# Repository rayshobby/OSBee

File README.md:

OpenSprinkler Bee (OSBee)
=========================

OpenSprinkler Bee (OSBee) is an open-source, Arduino-based sprinkler timer for battery-operated, latching solenoid valves. It's a great gadget for garden and lawn watering, plant and flower irrigation, and other watering applications. We provide two versions: 

- OSBee Shield: an Arduino shield with 4 independent zones
- OSBee: a standalone sprinkler timer with 4 independent zones and a 2.4GHz transceiver, powered by two AA batteries.

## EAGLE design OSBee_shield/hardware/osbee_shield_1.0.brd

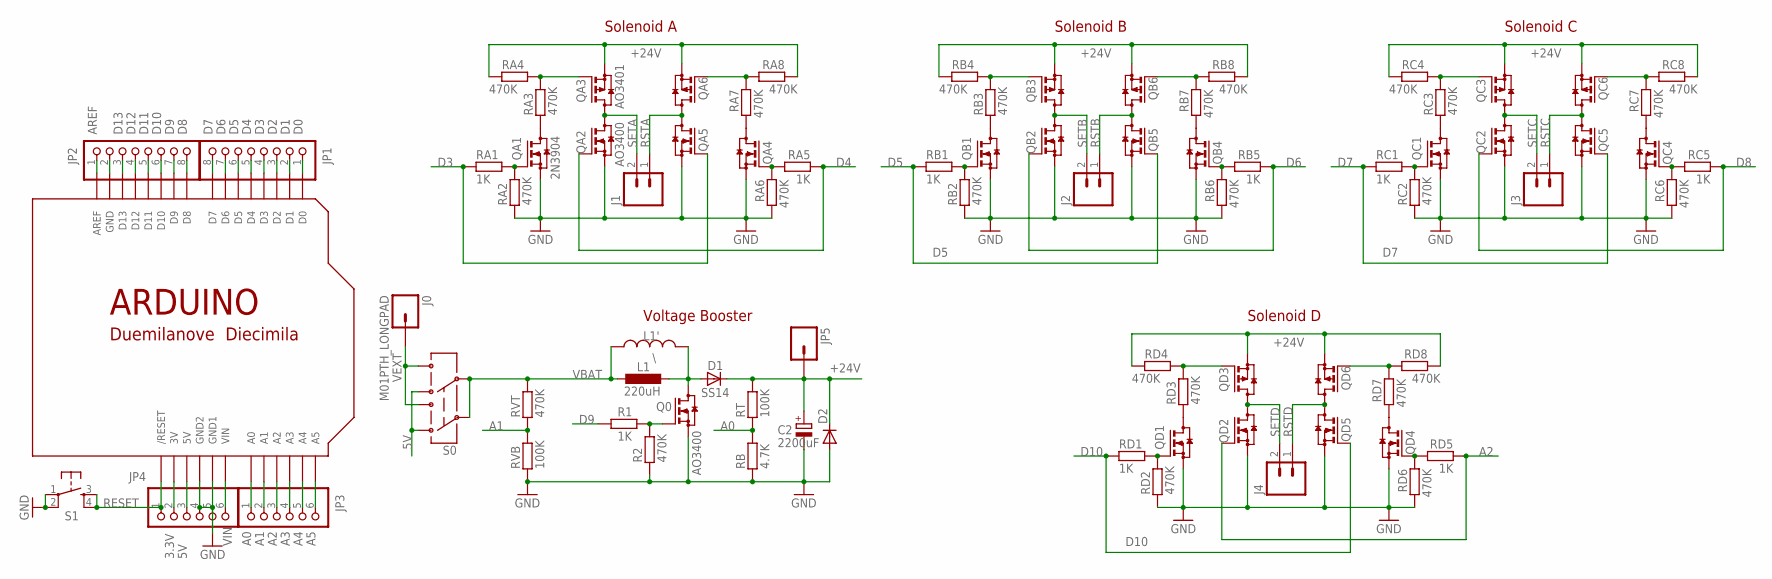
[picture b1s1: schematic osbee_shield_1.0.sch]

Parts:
C2: 2200uF; E5-13
D1: SS14; DO-214AC
D2: DIODE-MINIMELF; MINIMELF
J0: M01PTH_LONGPAD; 1X01_LONGPAD
J1, J2, J3, J4: M025MM; SCREWTERMINAL-5MM-2
JP1, JP2: PINHD-1X8BIG; 1X08-BIG
JP3, JP4: PINHD-1X6B; 1X06-BIG
JP5: M01SMDNS; 1X01NS
L1: 220uH; 0204/5
L1': \; INDUCTOR_D58
Q0: AO3400; SOT23
QA1: 2N3904; SOT23
QA2: AO3400; SOT23
QA3: AO3401; SOT23
QA4, QA5: BSS123; SOT23
QA6: BSS84; SOT23
QB1, QB2, QB4, QB5: BSS123; SOT23
QB3, QB6: BSS84; SOT23
QC1, QC2, QC4, QC5: BSS123; SOT23
QC3, QC6: BSS84; SOT23
QD1, QD2, QD4, QD5: BSS123; SOT23
QD3, QD6: BSS84; SOT23
R1: 1K; R0805
R2: 470K; R0805
RA1, RA5: 1K; R0805
RA2, RA3, RA4, RA6, RA7, RA8: 470K; R0805
RB: 4.7K; R0805
RB1, RB5: 1K; R0805
RB2, RB3, RB4, RB6, RB7, RB8: 470K; R0805
RC1, RC5: 1K; R0805
RC2, RC3, RC4, RC6, RC7, RC8: 470K; R0805
RD1, RD5: 1K; R0805
RD2, RD3, RD4, RD6, RD7, RD8: 470K; R0805
RT: 100K; R0805
RVB: 100K; R0805
RVT: 470K; R0805
S0: AYZ0202
S1: TAC_SWITCHPTH; TACTILE-PTH
U$1: ARDUINODUEMILANOVE-NODIM; ARDUINO-NODIM

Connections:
3.3V: JP4.2, U$1.3V
5V: JP4.3, S0.3 (1), S0.6 (4), U$1.5V
+24V: C2.+, D1.C, D2.C, JP5.1, QA3.2 (S), QA6.2 (S), QB3.2 (S), QB6.2 (S), QC3.2 (S), QC6.2 (S), QD3.2 (S), QD6.2 (S), RA4.2, RA8.2, RB4.2, RB8.2, RC4.2, RC8.2, RD4.2, RD8.2, RT.2
A0: JP3.1, RB.2, RT.1, U$1.A0
A1: JP3.2, RVB.2, RVT.1, U$1.A1
A2: JP3.3, QD2.1 (G), RD5.1, U$1.A2
A3: JP3.4, U$1.A3
A4: JP3.5, U$1.A4
A5: JP3.6, U$1.A5
AREF: JP2.1, U$1.AREF
D0: JP1.1, U$1.D0
D1: JP1.2, U$1.D1
D2: JP1.3, U$1.D2
D3: JP1.4, QA5.1 (G), RA1.1, U$1.D3
D4: JP1.5, QA2.1 (G), RA5.1, U$1.D4
D5: JP1.6, QB5.1 (G), RB1.1, U$1.D5
D6: JP1.7, QB2.1 (G), RB5.1, U$1.D6
D7: JP1.8, QC5.1 (G), RC1.1, U$1.D7
D8: JP2.8, QC2.1 (G), RC5.1, U$1.D8
D9: JP2.7, R1.2, U$1.D9
D10: JP2.6, QD5.1 (G), RD1.1, U$1.D10
D11: JP2.5, U$1.D11
D12: JP2.4, U$1.D12
D13: JP2.3, U$1.D13
GND: C2.-, D2.A, JP4.4, JP4.5, Q0.2 (S), QA1.2 (S), QA2.2 (S), QA4.2 (S), QA5.2 (S), QB1.2 (S), QB2.2 (S), QB4.2 (S), QB5.2 (S), QC1.2 (S), QC2.2 (S), QC4.2 (S), QC5.2 (S), QD1.2 (S), QD2.2 (S), QD4.2 (S), QD5.2 (S), R2.1, RA2.1, RA6.1, RB.1, RB2.1, RB6.1, RC2.1, RC6.1, RD2.1, RD6.1, RVB.1, S1.1, S1.2, U$1.GND1, U$1.GND2
unnamed: QA1.3 (D), RA3.1
unnamed: Q0.1 (G), R1.1, R2.2
unnamed: QB1.1 (G), RB1.2, RB2.2
unnamed: JP2.2, U$1.GND
unnamed: QB1.3 (D), RB3.1
unnamed: QB3.1 (G), RB3.2, RB4.1
unnamed: QA1.1 (G), RA1.2, RA2.2
unnamed: QB4.1 (G), RB5.2, RB6.2
unnamed: QA3.1 (G), RA3.2, RA4.1
unnamed: QA4.1 (G), RA5.2, RA6.2
unnamed: D1.A, L1.2, L1'.P$2 (2), Q0.3 (D)
unnamed: QB4.3 (D), RB7.1
unnamed: QA4.3 (D), RA7.1
unnamed: QA6.1 (G), RA7.2, RA8.1
unnamed: QB6.1 (G), RB7.2, RB8.1
unnamed: QC1.1 (G), RC1.2, RC2.2
unnamed: QC1.3 (D), RC3.1
unnamed: QC3.1 (G), RC3.2, RC4.1
unnamed: QC4.1 (G), RC5.2, RC6.2
unnamed: QC4.3 (D), RC7.1
unnamed: QC6.1 (G), RC7.2, RC8.1
unnamed: QD1.1 (G), RD1.2, RD2.2
unnamed: QD1.3 (D), RD3.1
unnamed: QD3.1 (G), RD3.2, RD4.1
unnamed: QD4.1 (G), RD5.2, RD6.2
unnamed: QD4.3 (D), RD7.1
unnamed: QD6.1 (G), RD7.2, RD8.1
RESET: JP4.1, S1.3, S1.4, U$1.RESET (/RESET)
RSTA: J1.1, QA5.3 (D), QA6.3 (D)
RSTB: J2.1, QB5.3 (D), QB6.3 (D)
RSTC: J3.1, QC5.3 (D), QC6.3 (D)
RSTD: J4.1, QD5.3 (D), QD6.3 (D)
SETA: J1.2, QA2.3 (D), QA3.3 (D)
SETB: J2.2, QB2.3 (D), QB3.3 (D)
SETC: J3.2, QC2.3 (D), QC3.3 (D)
SETD: J4.2, QD2.3 (D), QD3.3 (D)
VBAT: L1.1, L1'.P$1 (1), RVT.2, S0.2, S0.5
VEXT: J0.1, S0.1 (3), S0.4 (6)
VIN: JP4.6, U$1.VIN

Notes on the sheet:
Voltage Booster
Solenoid A
Solenoid B
Solenoid C
Solenoid D

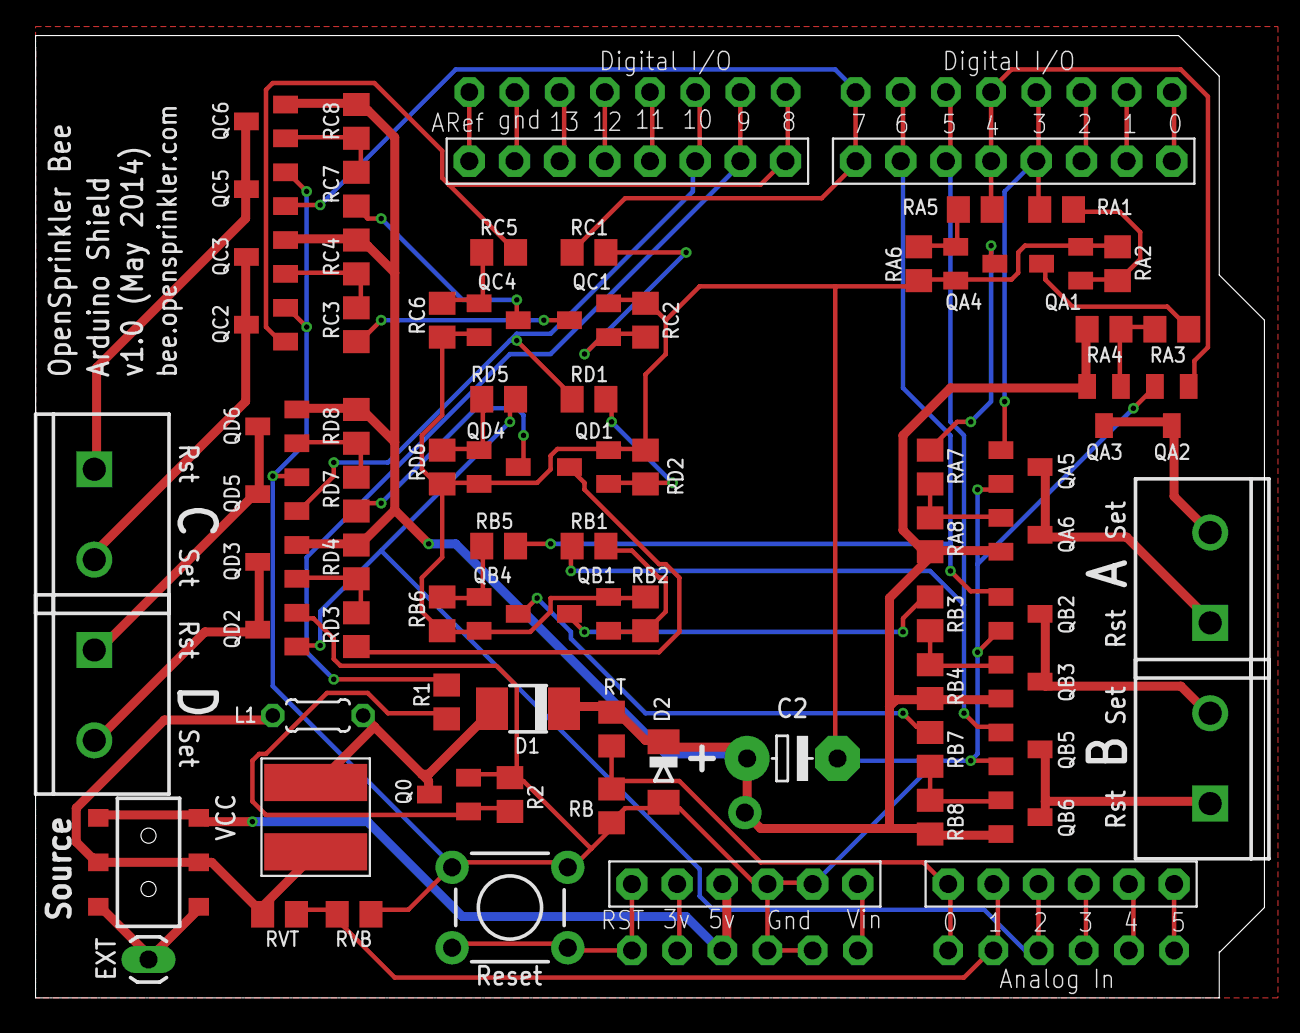
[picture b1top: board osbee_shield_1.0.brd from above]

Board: 2 copper layers, 69.1 x 54.1 mm, 81 parts (0 on the bottom side), 64 nets.

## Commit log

2014-05-28 check in OSBee_Shield hardware design files, Arduino library, and user manual
2014-05-28 update user manual
2014-06-01 fix a bug in the open by port number function

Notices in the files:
parts and their libraries:
SparkFunNew: Licensing: CC v3.0 Share-Alike You are welcome to use this library for commercial purposes.
